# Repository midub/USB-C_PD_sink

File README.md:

# USB-C Power Delivery sink
A board that negotiates voltage with PD compatible power supply.

				An easy way to bring USB-C power to your own project.

### Features
- Utilizes Cypress semiconductor's [CYPD3177](https://www.cypress.com/file/460416/download) IC.
- Tiny 32x16 mm board.
- Up to 3A current thanks to quality components.
- Set voltage by specified resistor value or by I2C.
- Access to I2C, GPIO_1, Interupt and Flip pins that are wired out to a 2x3 1.27mm pitch pin header.
- Screw holes next to usb-c port for better attachment.

### Todos
- Replace output power pins with fastons or othes suitable common connector.
- Create a design block, which can be used by powered board.

## DISCLAIMER: Use at your own risk

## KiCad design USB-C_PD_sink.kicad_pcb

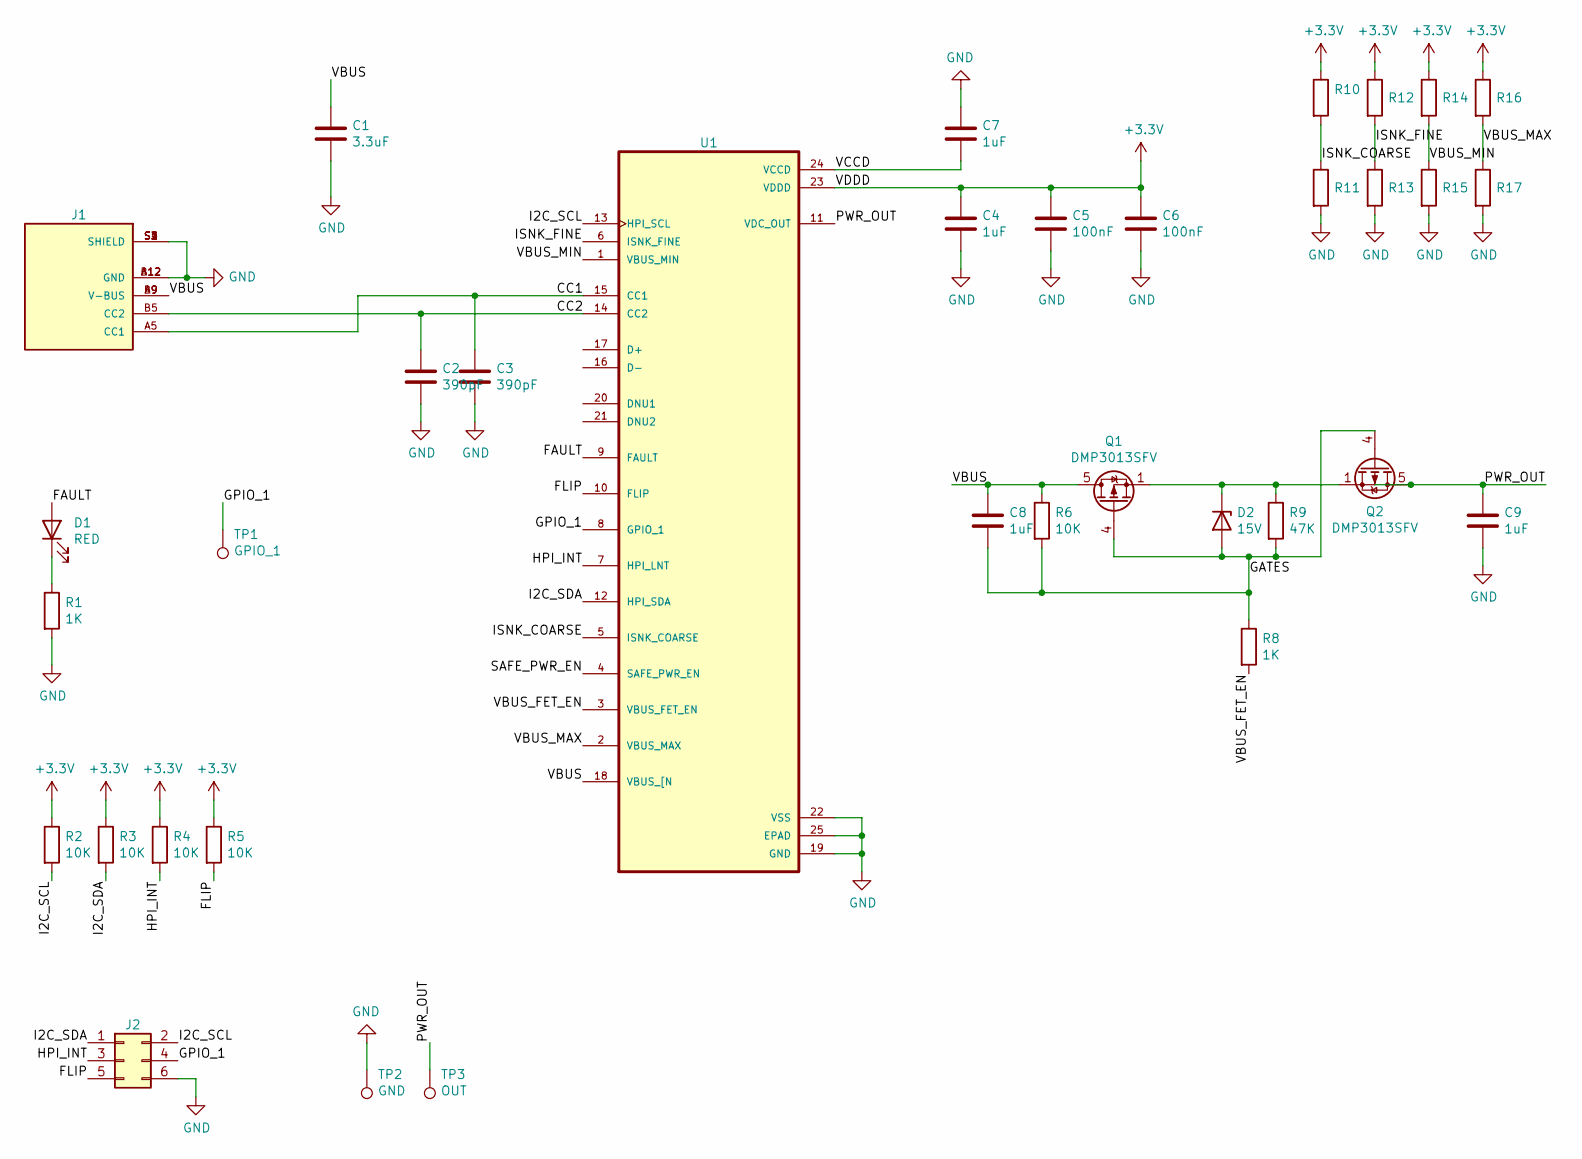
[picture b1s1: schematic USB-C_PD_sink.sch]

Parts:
C1: 3.3uF; C_0805_2012Metric
C2, C3: 390pF; C_0402_1005Metric
C4, C7, C8, C9: 1uF; C_0603_1608Metric
C5, C6: 100nF; C_0402_1005Metric
D1: RED; LED_0603_1608Metric_Castellated
D2: 15V; D_0805_2012Metric
J1: UJC-HP-3-SMT-TR; CUI_UJC-HP-3-SMT-TR; PARTREV 1.0
J2: Conn_02x03_Odd_Even; PinHeader_2x03_P2.00mm_Horizontal
Q1, Q2: DMP3013SFV; Diodes_PowerDI3333-8
R1, R8: 1K; R_0402_1005Metric
R2, R3, R4, R5, R6: 10K; R_0402_1005Metric
R9: 47K; R_0402_1005Metric
R10, R11, R12, R13, R14, R15, R16, R17: OPT; R_0402_1005Metric
TP1: GPIO_1; TestPoint_Pad_D2.0mm
TP2: GND; TestPoint_THTPad_3.0x3.0mm_Drill1.5mm
TP3: OUT; TestPoint_THTPad_3.0x3.0mm_Drill1.5mm
U1: CYPD3177-24LQXQ; QFN50P400X400X60-25N

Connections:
+3V3: C4.1, C5.1, C6.1, R2.1, R3.1, R4.1, R5.1, R10.1, R12.1, R14.1, R16.1, U1.23 (VDDD)
/CC1: C3.1, J1.A5 (CC1), U1.15 (CC1)
/CC2: C2.1, J1.B5 (CC2), U1.14 (CC2)
/FAULT: D1.2 (A), U1.9 (FAULT)
/FLIP: J2.5, R5.2, U1.10 (FLIP)
/GATES: C8.2, D2.2 (A), Q1.4 (G), Q2.4 (G), R6.2, R8.1, R9.2
/GPIO_1: J2.4, TP1.1, U1.8 (GPIO_1)
/HPI_INT: J2.3, R4.2, U1.7 (HPI_LNT)
/I2C_SCL: J2.2, R2.2, U1.13 (HPI_SCL)
/I2C_SDA: J2.1, R3.2, U1.12 (HPI_SDA)
/ISNK_COARSE: R10.2, R11.1, U1.5 (ISNK_COARSE)
/ISNK_FINE: R12.2, R13.1, U1.6 (ISNK_FINE)
/PWR_OUT: C9.1, Q2.5 (D), TP3.1, U1.11 (VDC_OUT); also elsewhere on the board
/SAFE_PWR_EN: U1.4 (SAFE_PWR_EN)
/VBUS: C1.1, C8.1, J1.A9 (V-BUS), J1.B9 (V-BUS), Q1.5 (D), R6.1, U1.18 (VBUS_[N)
/VBUS_FET_EN: R8.2, U1.3 (VBUS_FET_EN)
/VBUS_MAX: R16.2, R17.1, U1.2 (VBUS_MAX)
/VBUS_MIN: R14.2, R15.1, U1.1 (VBUS_MIN)
/VCCD: C7.2, U1.24 (VCCD)
GND: C1.2, C2.2, C3.2, C4.2, C5.2, C6.2, C7.1, C9.2, J1.A12 (GND), J1.B12 (GND), J1.S1 (SHIELD), J1.S2 (SHIELD), J1.S3 (SHIELD), J1.S4 (SHIELD), J2.6, R1.2, R11.2, R13.2, R15.2, R17.2, TP2.1, U1.19 (GND), U1.22 (VSS), U1.25 (EPAD); also elsewhere on the board
unnamed: D1.1 (K), R1.1
unnamed: D2.1 (K), Q1.1 (S), Q1.2 (S), Q1.3 (S), Q2.1 (S), Q2.2 (S), Q2.3 (S), R9.1

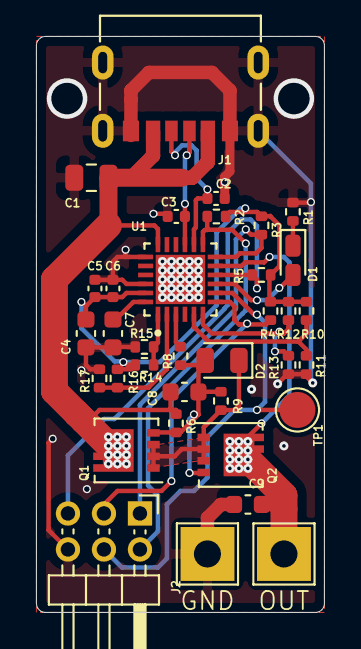
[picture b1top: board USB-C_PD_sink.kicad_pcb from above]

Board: 2 copper layers, 16.0 x 32.0 mm, 35 parts (0 on the bottom side), 21 nets.

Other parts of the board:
GND: GND; TestPoint_THTPad_3.0x3.0mm_Drill1.5mm
OUT: OUT; TestPoint_THTPad_3.0x3.0mm_Drill1.5mm

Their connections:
/PWR_OUT: OUT.1; also elsewhere on the board
GND: GND.1; also elsewhere on the board

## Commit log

2020-12-29 Initial
    Adds revision 1 files
2020-12-29 Updates readme
